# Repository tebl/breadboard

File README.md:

# Breadboard
I had to move lately, so there was a lot of sorting going on in order to determine the things to bring and the items to let go off. A few of them are projects that only exist on breadboards in some form, so either I had to stuff them into a box and hope for the best or transfer the designs into a more durable medium. For the ones where I didn't want to design something specific yet, I instead wanted to transfer them directly and for that purpose I made these breadboard analogs so that I could transfer them directly.

The later added 830 point version of should be perfect for when you've tested individual modules while following the Ben Eater series, both the 8 bit computer as well as the 6502 builds (BE6502 is my version of this). Numbers have been indicated on both sides as well as a near identical layout, this should make transferring the design close to error-free. Use the M3 holes at the center to mount the breadboard PCBs, making it suitable for hanging on a wall etc.

You can have these made at your vendor of choice, mostly by handing the zipped contents of each versions export directory to them (usually referred to as gerber files). If it is possible, I would prefer that you use the links below as that'll give me a discount (allowing me the ability to keep my projects open and available to anyone).

| Reference      | Item                         | Order      |
| -------------- | ---------------------------- | ---------- |
| Breadboard 400 | Fabricate using Gerber files | [PCBWay](https://www.pcbway.com/project/shareproject/Breadboard_400.html) |
| Breadboard 830 | Fabricate using Gerber files | [PCBWay](https://www.pcbway.com/project/shareproject/Breadboard_830.html) |

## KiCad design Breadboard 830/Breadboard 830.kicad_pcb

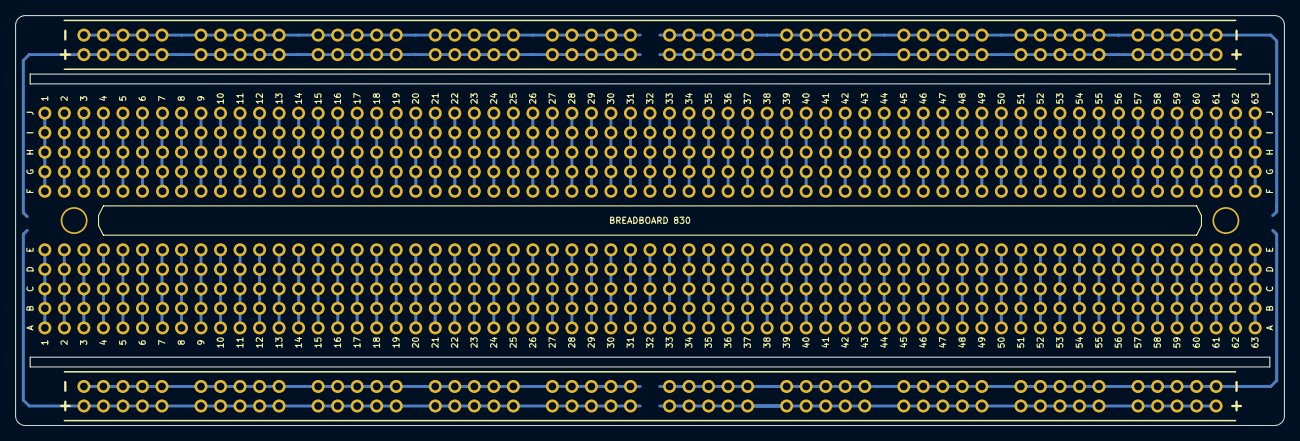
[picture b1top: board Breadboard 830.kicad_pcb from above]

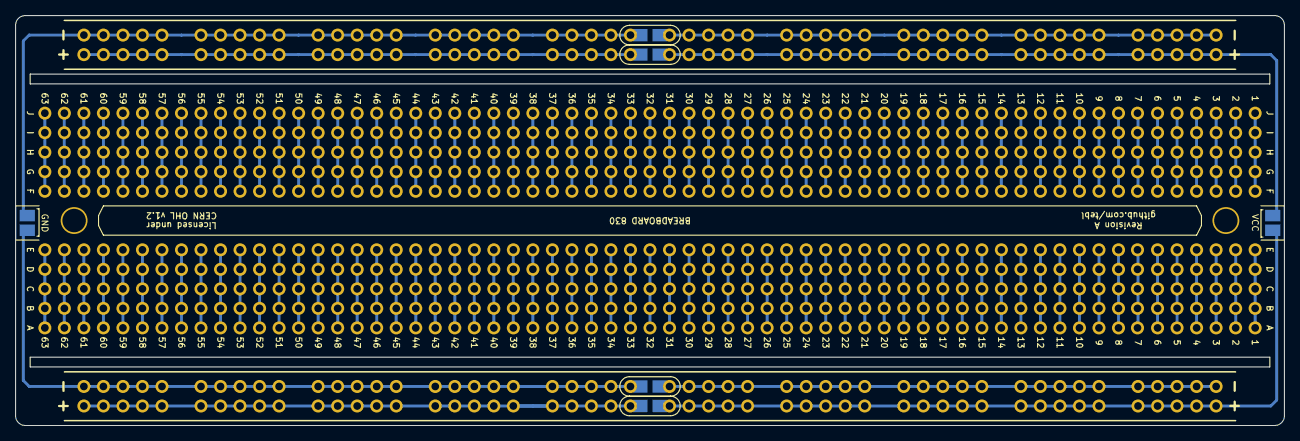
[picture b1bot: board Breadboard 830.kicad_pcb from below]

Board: 2 copper layers, 165.1 x 53.3 mm, 91 parts (6 on the bottom side), 8 nets.

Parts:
A1, A2, A3, A4, A5, A6, A7, A8, A9, A10, A11, A12, A13, A14, A15, A16, A17, A18, A19, A20: PWR; power
A21, A22, A23, A24, A25, A26, A27, A28, A29, A30, A31, A32, A33, A34, A35, A36, A37, A38, A39, A40, A41, A42, A43, A44, A45, A46, A47, A48, A49, A50, A51, A52, A53, A54, A55, A56, A57, A58, A59, A60, A61, A62, A63, A64, A65, A66, A67, A68, A69, A70, A71, A72, A73, A74, A75, A76, A77, A78, A79, A80, A81, A82, A83: BB; section
H1, H2: MountingHole; M3
JP1, JP3: LINK_GND; bridge2
JP2, JP4: LINK_VCC; bridge2
JP5: LINK_VCC; bridge
JP6: LINK_GND; bridge

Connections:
/GND1: A1.2, A2.2, A3.2, A4.2, A5.2, JP1.1
/GND2: A6.2, A7.2, A8.2, A9.2, A10.2, JP1.2, JP6.2
/GND3: A11.2, A12.2, A13.2, A14.2, A15.2, JP3.1
/GND4: A16.2, A17.2, A18.2, A19.2, A20.2, JP3.2, JP6.1
/VCC1: A1.1, A2.1, A3.1, A4.1, A5.1, JP2.1, JP5.1
/VCC2: A6.1, A7.1, A8.1, A9.1, A10.1, JP2.2
/VCC3: A11.1, A12.1, A13.1, A14.1, A15.1, JP4.1, JP5.2
/VCC4: A16.1, A17.1, A18.1, A19.1, A20.1, JP4.2

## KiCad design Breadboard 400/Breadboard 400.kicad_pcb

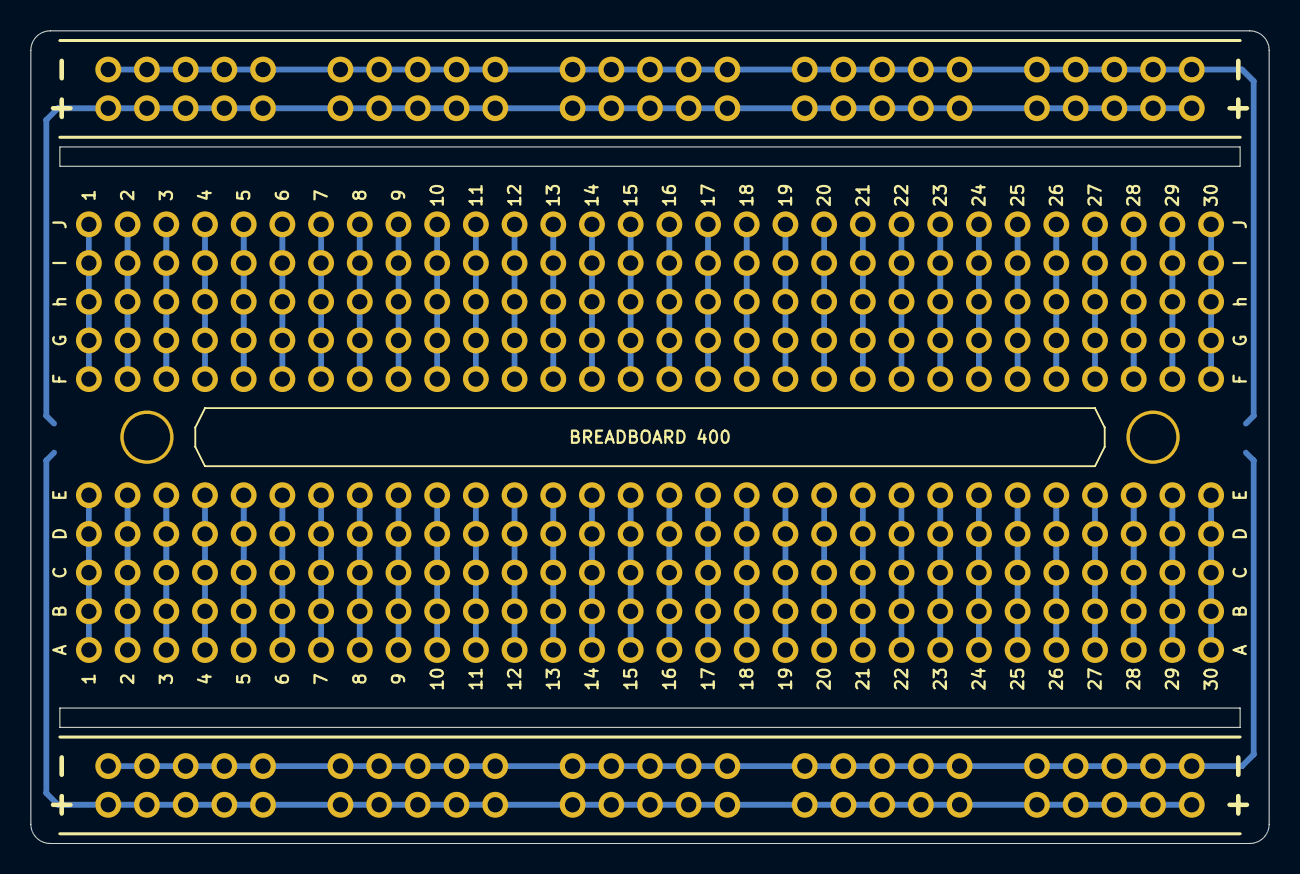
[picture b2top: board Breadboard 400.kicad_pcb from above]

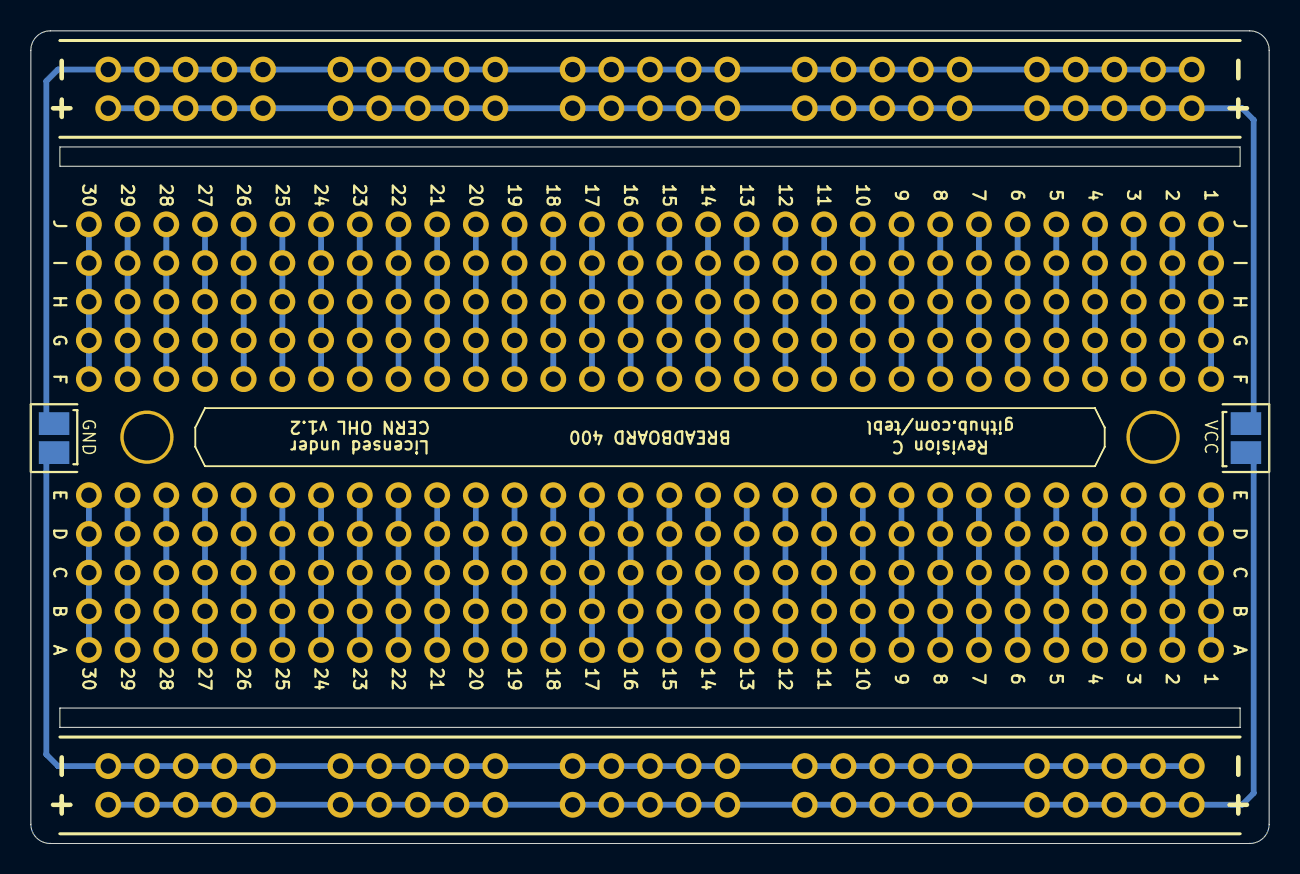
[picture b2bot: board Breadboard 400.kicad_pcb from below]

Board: 2 copper layers, 81.3 x 53.3 mm, 44 parts (2 on the bottom side), 4 nets.

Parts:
A1, A2, A3, A4, A5, A11, A12, A13, A14, A15: PWR; power
A6, A7, A8, A9, A10, A16, A17, A18, A19, A20, A21, A22, A23, A24, A25, A26, A27, A28, A29, A30, A31, A32, A33, A34, A35, A36, A37, A38, A39, A40: BB; section
H1, H2: MountingHole; M3
JP5: LINK_VCC; bridge
JP6: LINK_GND; bridge

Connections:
/GND1: A1.2, A2.2, A3.2, A4.2, A5.2, JP6.2
/GND2: A11.2, A12.2, A13.2, A14.2, A15.2, JP6.1
/VCC1: A1.1, A2.1, A3.1, A4.1, A5.1, JP5.1
/VCC2: A11.1, A12.1, A13.1, A14.1, A15.1, JP5.2

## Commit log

2020-07-12 400 point breadboard
2020-11-06 Fixed problems with the first one
2020-11-06 README and license added.
2020-11-06 Removed file
2020-11-06 Added fab details
2021-02-07 Breadboard 830
2021-02-07 Gerber export

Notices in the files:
Breadboard 400/Breadboard 400.kicad_pcb:
Licensed under
CERN OHL v1.2
